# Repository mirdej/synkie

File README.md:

The Synkie is a modular open source analog video processor, developed by Michael Egger, Max Egger and Flo Kaufmann. A bit like the venerable modular Moog synthesizer it lets you toy around with the signal using patch cables – but this time not producing sound but images. It is an instrument for video, a playground, a platform to explore new ways to transform a video signal. Synkie is still in development, we constantly develop new modules – and even the base specifications may still change over time. 

Synkie’s main goal is playability not image quality, even though we try to design each module as best as we can. But patching is done with 2mm laboratory cables – not shielded 75Ohm BNC cables as one would normally use for video. No, you can even use any blank wire and tinker around with the signal in real time on the sk90-breadboard module… The laboratory plugs can be stacked, so you can easily divide the signal into multiple paths, feeding multiple modules at once and change the configuration on the fly. The resulting image can get quite messy down the road, but that’s part of the fun, or maybe even the main purpose…

# Before building stuff from here yourself - read this:

This Github repository is our working space and not a DIY tutorial. Lots of stuff is completely outdated and/or poorly documented. Here are some important notes about the current state of things (Oct 2021):

- Pretty much everything in the EAGLE directory is totally obsolete and we only keep it for documentation.

- We settled on the LMH6643 as our Opamp of choice for almost everything where frequency response matters. Not all schematics reflect this. In most cases if there's an opamp named "generic opamp" or even "LM833" - we probably meant LMH6643.

- There are several modules where the supply connector is flipped. As we etch a lot of boards ourselves there is no silkscreen and we don't see the error. ALWAYS check the polarity !

- We live in PAL land. These modules have not beent tested with NTSC video. Some might need to be adapted slightly, some might even work better than here ;-)

If you have any questions contact <info@synkie.net>

# Basics

## Synkie Backbone
Modules sk000 to sk009 constitute the Synkie Backbone – handling Ins out Outs to the normal Video World. Input video is clamped (black level = GND) and stripped of timing signals and color burst. This signal can then be fed to any processing modules.
In the end , timing signals and a phase corrected color burst is cut back into the modified signal, in sync with the Genlock input.

### sk000-power
Power distribution to backbone modules and rack. +5V, GND, -5V.

### sk001-genlock-in

This module takes any standard video signal as input and generates all necessary timing signals for the Synkie system. The input is first backporch-clamped to GND and all active video is cut off. This black image can serve as a genlock for connected sources (cameras). Colorburst is output as a seperate signal and used to syncronise a quartz crystal that generates a continuous 4.4336Mhz subcarrier signal for the rgb modules. A LM1881 generates the digital sync signals: horizontal sync, vertical sync, backporch and odd/even.

### sk002-input

This modules takes any standard video signal, clamps black level to GND and strips off synctips and colorburst. (still in active debate: me thinks sk002 should apply a gain of 1.43 to bring the 0.7V white level up to 1V)

### sk003-output

This module takes any signal as its input (from DC to 10Mhz). The scale-bias section controls amplitude and dc-shift. The signal is then clipped hard between 0V and 1V. Finally the resyncer adds synctips and colorburst to make it look like a standard video signal. 
When using video as an input to the sk003 any processing beforehand can add some tiny delay - depending on how many modules the signal passes through -  which causes a phase shift in the signal that can alter or completely destroy color. That is why the burst signal from sk001 first goes through a sk004-burstshift (allpass filter) that lets correct the phase error before it gets cut back into the video signal.

## Synkie Signals

### Terminology
| Signal name | Waveform| Description  |Specs|
|---|---|---|---|
|Genlock||A video signal that serves as the master synchronisation signal. Can be routed through and used as an input.|-0.3V to 0.7V|
|Video||Standard PAL video signal|-0.3V to 0.7V|
|Sync| |Digital sync pulses: H-Sync, V-Sync, Backporch, Odd/Even|0V to 5V|
|Burst|| Colorburst only, AC coupled|ca. -0.1V to 0.1V|
|Siff| |Synkie signal. Can be anything, DC, CV, Audio or Video. 0V means black. 1V means white|-1V to 1V|

### The SIFF signal
Synkie's goal is to be able to mix all signals, be it control signals, audio or picture. You should be able to use a video image as control voltage for a VCO like you should be able to inject a sound into the video or watch a steady 0.256 volts.

* Siff signals are DC coupled. 0V means black. 1V means white.
* Siff signals can still be negative, meaning superblack or substracting signals !
* Siff signals can be loud - going beyond 1V and below -1V. The sk003-output module will finally limit the signal to 0-1V.
* Siff signals can range from DC (0Hz) to ca. 10Mhz

This has the following implications for synkie modules:

* All module inputs should be high-impedance, DC coupled and ESR protected.
* All module outputs should be low-impedance and DC coupled.
* Whenever possible a module's bandwidth should be at least 4Mhz
* Sensible CV range should be between 0V and 1V.
* But: Modules must be able to cope with voltages as low as -5V to as high as 5V
* Gate signals are 0V to 1V !!
* So: trigger inputs should trigger at around 0.5V ! Use comparators.

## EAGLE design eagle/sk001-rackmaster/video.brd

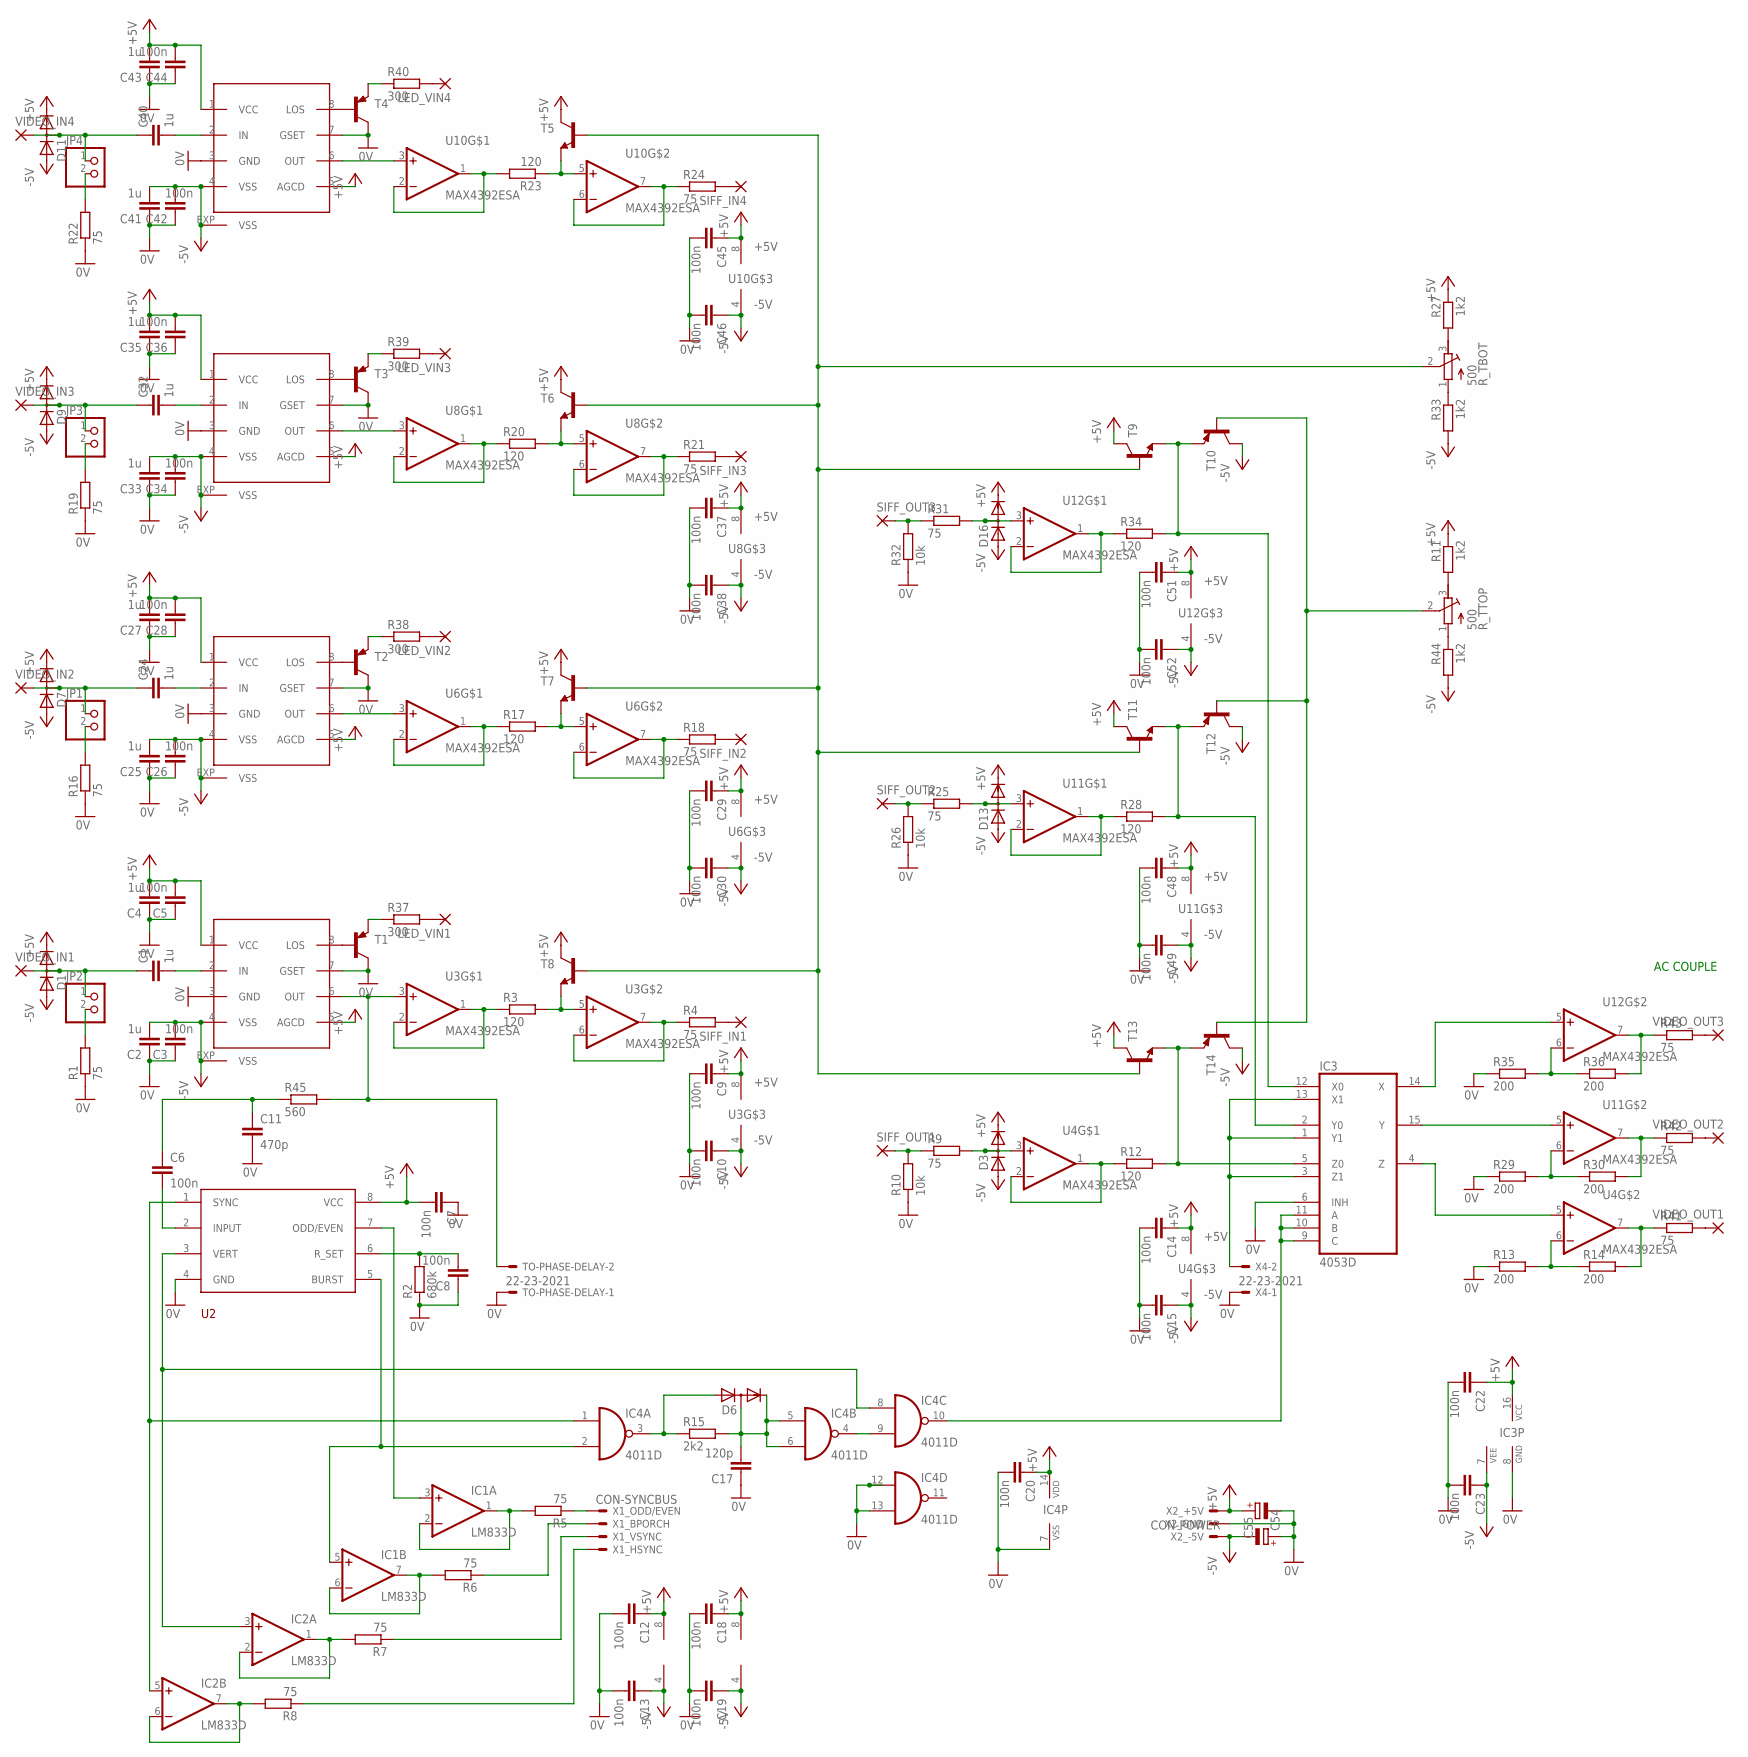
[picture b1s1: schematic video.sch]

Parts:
C1, C2, C4, C24, C25, C27, C32, C33, C35, C40, C41, C43: 1u; C0805
C3, C5, C6, C7, C8, C9, C10, C12, C13, C14, C15, C18, C19, C20, C22, C23, C26, C28, C29, C30, C34, C36, C37, C38, C42, C44, C45, C46, C48, C49, C51, C52: 100n; C0805
C11: 470p; C0805
C17: 120p; C0805
C54, C55: CPOL-EUCT3528; CT3528
D1, D3, D6, D7, D9, D11, D13, D16: DIODE_2CACA-SOT23; SOT23
IC1, IC2: LM833D; SO08
IC3: 4053D; SO16
IC4: 4011D; SO14
JP1, JP2, JP3, JP4: PINHD-1X2; 1X02
LED_VIN1, LED_VIN2, LED_VIN3, LED_VIN4: 3,17/1,1
R1, R4, R5, R6, R7, R8, R9, R16, R18, R19, R21, R22, R24, R25, R31, R41, R42, R43: 75; R0805
R2: 680k; R0805
R3, R12, R17, R20, R23, R28, R34: 120; R0805
R10, R26, R32: 10k; R0805
R11, R27, R33, R44: 1k2; R0805
R13, R14, R29, R30, R35, R36: 200; R0805
R15: 2k2; R0805
R37, R38, R39, R40: 300; R0805
R45: 560; R0805
R_TBOT: 500; RTRIM64Y
R_TTOP: 500; RTRIM64Y
SIFF_IN1, SIFF_IN2, SIFF_IN3, SIFF_IN4: 3,17/1,1
SIFF_OUT1, SIFF_OUT2, SIFF_OUT3: 3,17/1,1
T1, T2, T3, T4, T10, T12, T14: TRANS-PNPSOT23-BEC; SOT23-BEC
T5, T6, T7, T8, T9, T11, T13: TRANS-NPN; SOT23-BEC
TO-PHASE-DELAY: 22-23-2021
U1, U5, U7, U9: MAX7450; SO08-EXP
U2: LM1881SO8; SO08
U3, U4, U6, U8, U10, U11, U12: MAX4392ESA; SO08
VIDEO_IN1, VIDEO_IN2, VIDEO_IN3, VIDEO_IN4: 3,17/1,1
VIDEO_OUT1, VIDEO_OUT2, VIDEO_OUT3: 3,17/1,1
X1: CON-SYNCBUS; 22-23-2041
X2: CON-POWER; 22-23-2031
X4: 22-23-2021

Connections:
0V: C2.1, C3.1, C4.1, C5.1, C7.1, C8.1, C9.2, C10.2, C11.2, C12.2, C13.2, C14.2, C15.2, C17.1, C18.2, C19.2, C20.2, C22.2, C23.2, C25.1, C26.1, C27.1, C28.1, C29.2, C30.2, C33.1, C34.1, C35.1, C36.1, C37.2, C38.2, C41.1, C42.1, C43.1, C44.1, C45.2, C46.2, C48.2, C49.2, C51.2, C52.2, C54.+, C55.-, IC3.6 (INH), IC3.8 (GND), IC4.7 (VSS), IC4.12 (I0), IC4.13 (I1), R1.1, R2.1, R10.1, R13.1, R16.1, R19.1, R22.1, R26.1, R29.1, R32.1, R35.1, T1.C, T2.C, T3.C, T4.C, TO-PHASE-DELAY.1, U1.3 (GND), U1.7 (GSET), U2.4 (GND), U5.3 (GND), U5.7 (GSET), U7.3 (GND), U7.7 (GSET), U9.3 (GND), U9.7 (GSET), X2.2, X4.1
+5V: C4.2, C5.2, C7.2, C9.1, C12.1, C14.1, C18.1, C20.1, C22.1, C27.2, C28.2, C29.1, C35.2, C36.2, C37.1, C43.2, C44.2, C45.1, C48.1, C51.1, C55.+, D1.2 (C), D3.2 (C), D7.2 (C), D9.2 (C), D11.2 (C), D13.2 (C), D16.2 (C), IC1.8 (V+), IC2.8 (V+), IC3.16 (VCC), IC4.14 (VDD), R11.1, R27.1, T5.C, T6.C, T7.C, T8.C, T9.C, T11.C, T13.C, U1.1 (VCC), U1.5 (AGCD), U2.8 (VCC), U3.8 (+5V), U4.8 (+5V), U5.1 (VCC), U5.5 (AGCD), U6.8 (+5V), U7.1 (VCC), U7.5 (AGCD), U8.8 (+5V), U9.1 (VCC), U9.5 (AGCD), U10.8 (+5V), U11.8 (+5V), U12.8 (+5V), X2.3
-5V: C2.2, C3.2, C10.1, C13.1, C15.1, C19.1, C23.1, C25.2, C26.2, C30.1, C33.2, C34.2, C38.1, C41.2, C42.2, C46.1, C49.1, C52.1, C54.-, D1.1 (A), D3.1 (A), D7.1 (A), D9.1 (A), D11.1 (A), D13.1 (A), D16.1 (A), IC1.4 (V-), IC2.4 (V-), IC3.7 (VEE), R33.2, R44.2, T10.C, T12.C, T14.C, U1.4 (VSS), U1.EXP (VSS), U3.4 (-5V), U4.4 (-5V), U5.4 (VSS), U5.EXP (VSS), U6.4 (-5V), U7.4 (VSS), U7.EXP (VSS), U8.4 (-5V), U9.4 (VSS), U9.EXP (VSS), U10.4 (-5V), U11.4 (-5V), U12.4 (-5V), X2.1
H: IC2.5 (+IN), IC4.1 (I0), U2.1 (SYNC)
unnamed: IC3.4 (Z), U4.5 (+IN)
unnamed: JP2.2, R1.2
unnamed: C6.2, U2.2 (INPUT)
unnamed: C8.2, R2.2, U2.6 (R_SET)
unnamed: C1.2, U1.2 (IN)
unnamed: IC1.1 (OUT), IC1.2 (-IN), R5.2
unnamed: R45.2, TO-PHASE-DELAY.2, U1.6 (OUT), U3.3 (+IN)
unnamed: R3.1, U3.1 (OUT), U3.2 (-IN)
unnamed: R3.2, T8.E, U3.5 (+IN)
unnamed: R4.1, U3.6 (-IN), U3.7 (OUT)
unnamed: R4.2, SIFF_IN1.1
unnamed: IC1.6 (-IN), IC1.7 (OUT), R6.2
unnamed: IC2.1 (OUT), IC2.2 (-IN), R7.2
unnamed: IC2.6 (-IN), IC2.7 (OUT), R8.2
unnamed: R6.1, X1.2
unnamed: R5.1, X1.1
unnamed: R7.1, X1.3
unnamed: R8.1, X1.4
unnamed: C6.1, C11.1, R45.1
unnamed: IC1.5 (+IN), IC4.2 (I1), U2.5 (BURST)
unnamed: IC2.3 (+IN), IC4.8 (I0), U2.3 (VERT)
unnamed: R9.1, R10.2, SIFF_OUT1.1
unnamed: D3.3 (AC), R9.2, U4.3 (+IN)
unnamed: R12.1, U4.1 (OUT), U4.2 (-IN)
unnamed: IC3.5 (Z0), R12.2, T13.E, T14.E
unnamed: R27.2, R_TBOT.3 (E)
unnamed: R13.2, R14.1, U4.6 (-IN)
unnamed: C1.1, D1.3 (AC), JP2.1, VIDEO_IN1.1
unnamed: R14.2, R41.1, U4.7 (OUT)
unnamed: IC4.4 (O), IC4.9 (I1)
unnamed: D6.1 (A), IC4.3 (O), R15.1
unnamed: C17.2, D6.2 (C), D6.3 (AC), IC4.5 (I0), IC4.6 (I1), R15.2
unnamed: JP1.2, R16.2
unnamed: R25.1, R26.2, SIFF_OUT2.1
unnamed: C24.2, U5.2 (IN)
unnamed: U5.6 (OUT), U6.3 (+IN)
unnamed: R17.1, U6.1 (OUT), U6.2 (-IN)
unnamed: R17.2, T7.E, U6.5 (+IN)
unnamed: R18.1, U6.6 (-IN), U6.7 (OUT)
unnamed: R18.2, SIFF_IN2.1
unnamed: C24.1, D7.3 (AC), JP1.1, VIDEO_IN2.1
unnamed: JP3.2, R19.2
unnamed: C32.2, U7.2 (IN)
unnamed: U7.6 (OUT), U8.3 (+IN)
unnamed: R20.1, U8.1 (OUT), U8.2 (-IN)
unnamed: R20.2, T6.E, U8.5 (+IN)
unnamed: R21.1, U8.6 (-IN), U8.7 (OUT)
unnamed: R21.2, SIFF_IN3.1
unnamed: C32.1, D9.3 (AC), JP3.1, VIDEO_IN3.1
unnamed: JP4.2, R22.2
unnamed: C40.2, U9.2 (IN)
unnamed: U9.6 (OUT), U10.3 (+IN)
unnamed: R23.2, U10.1 (OUT), U10.2 (-IN)
unnamed: R23.1, T5.E, U10.5 (+IN)
unnamed: R24.1, U10.6 (-IN), U10.7 (OUT)
unnamed: R24.2, SIFF_IN4.1
unnamed: C40.1, D11.3 (AC), JP4.1, VIDEO_IN4.1
unnamed: IC3.9 (C), IC3.10 (B), IC3.11 (A), IC4.10 (O)
unnamed: D13.3 (AC), R25.2, U11.3 (+IN)
unnamed: R28.1, U11.1 (OUT), U11.2 (-IN)
unnamed: R_TTOP.2 (S), T10.B, T12.B, T14.B
unnamed: R33.1, R_TBOT.1 (A)
unnamed: R29.2, R30.1, U11.6 (-IN)
unnamed: R30.2, R42.1, U11.7 (OUT)
unnamed: IC3.15 (Y), U11.5 (+IN)
unnamed: R31.1, R32.2, SIFF_OUT3.1
unnamed: D16.3 (AC), R31.2, U12.3 (+IN)
unnamed: R34.1, U12.1 (OUT), U12.2 (-IN)
unnamed: IC3.12 (X0), R34.2, T9.E, T10.E
unnamed: R11.2, R_TTOP.3 (E)
unnamed: R35.2, R36.1, U12.6 (-IN)
unnamed: R36.2, R43.1, U12.7 (OUT)
unnamed: IC3.14 (X), U12.5 (+IN)
unnamed: R37.1, T1.E
unnamed: LED_VIN1.1, R37.2
unnamed: T1.B, U1.8 (LOS)
unnamed: R38.1, T2.E
unnamed: LED_VIN2.1, R38.2
unnamed: T2.B, U5.8 (LOS)
unnamed: R39.1, T3.E
unnamed: LED_VIN3.1, R39.2
unnamed: T3.B, U7.8 (LOS)
unnamed: R40.1, T4.E
unnamed: LED_VIN4.1, R40.2
unnamed: T4.B, U9.8 (LOS)
unnamed: R41.2, VIDEO_OUT1.1
unnamed: R42.2, VIDEO_OUT2.1
unnamed: R43.2, VIDEO_OUT3.1
unnamed: IC3.1 (Y1), IC3.3 (Z1), IC3.13 (X1), X4.2
unnamed: R_TBOT.2 (S), T5.B, T6.B, T7.B, T8.B, T9.B, T11.B, T13.B
unnamed: IC3.2 (Y0), R28.2, T11.E, T12.E
unnamed: R44.1, R_TTOP.1 (A)
O!E: IC1.3 (+IN), U2.7 (ODD/EVEN)

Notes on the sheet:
AC COUPLE

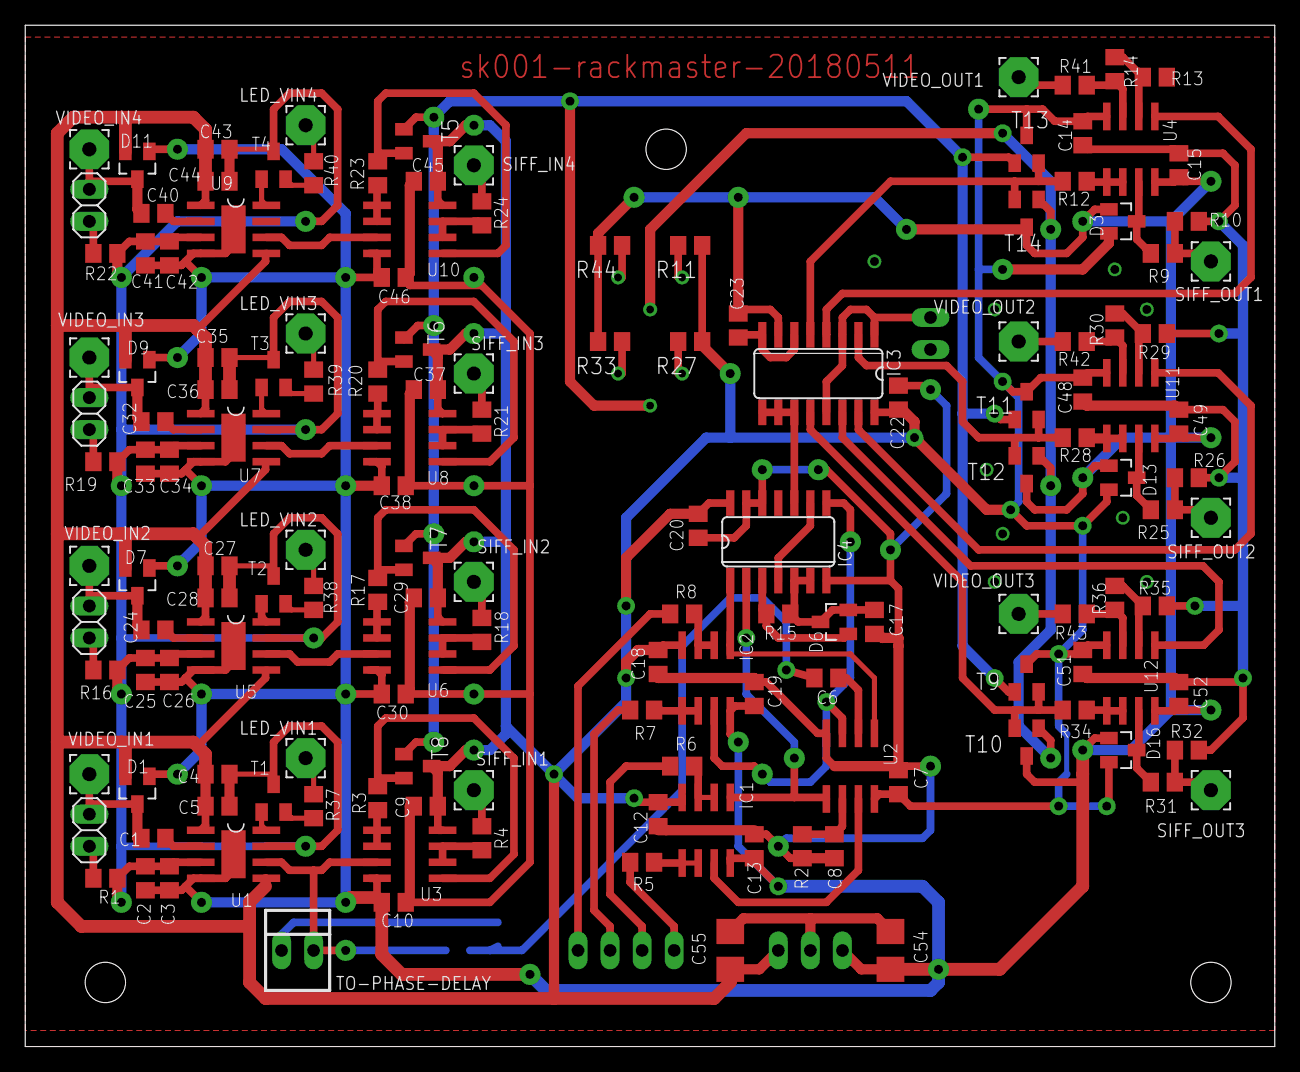
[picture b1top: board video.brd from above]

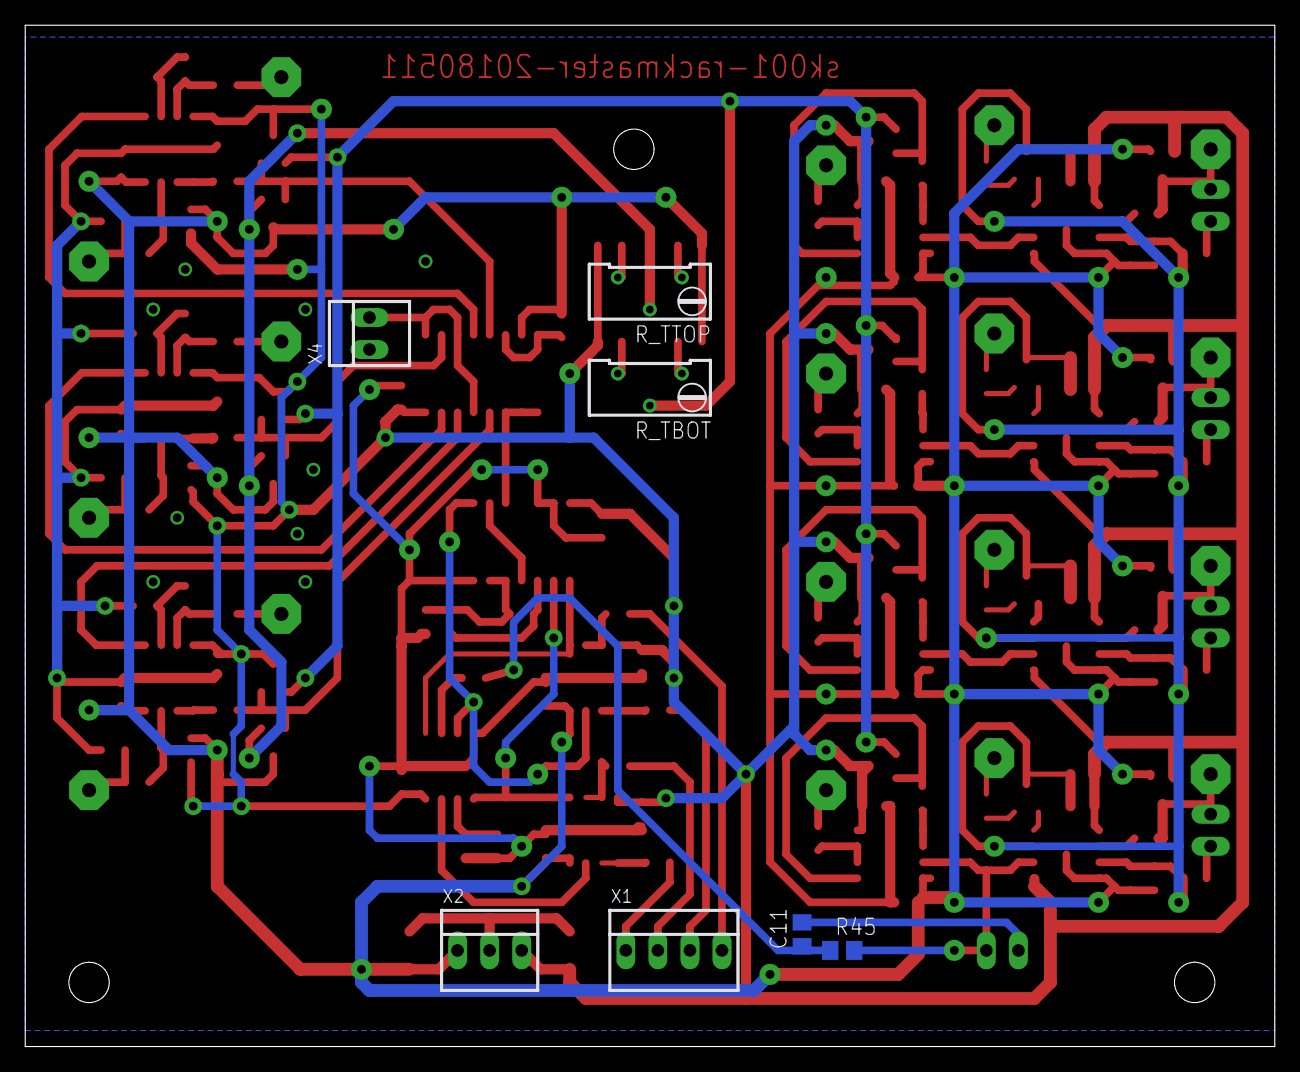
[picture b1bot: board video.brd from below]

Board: 2 copper layers, 99.0 x 81.0 mm, 159 parts (7 on the bottom side), 97 nets.

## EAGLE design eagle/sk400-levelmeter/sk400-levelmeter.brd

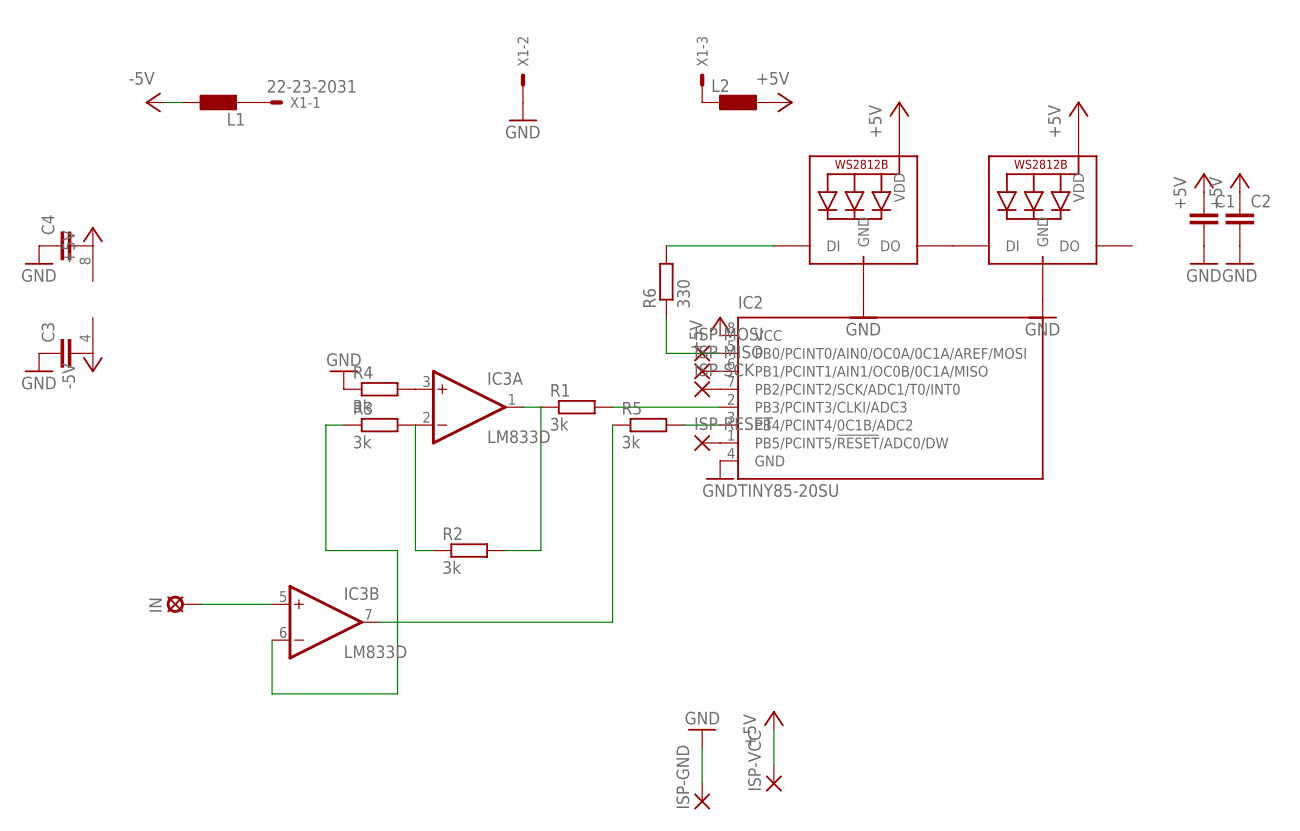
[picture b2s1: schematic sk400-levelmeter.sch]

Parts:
C1, C3, C4: C-EUC1206; C1206
C2: C-EUC0603; C0603
IC2: TINY85-20SU; 8S2
IC3: LM833D; SO08
IN: LSP13
ISP-GND: SMD2
ISP-MISO: SMD2
ISP-MOSI: SMD2
ISP-RESET: SMD2
ISP-SCK: SMD2
ISP-VCC: SMD2
L1, L2: LL2012C; L2012C
R1, R2, R3, R4, R5: 3k; R1206
R6: 330; R1206
U$1, U$2: SK6812MINI
X1: 22-23-2031

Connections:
+5V: C1.1, C2.1, C4.2, IC2.8 (VCC), IC3.8 (V+), ISP-VCC.1, L2.1, U$1.4 (VDD), U$2.4 (VDD)
-5V: C3.2, IC3.4 (V-), L1.1
GND: C1.2, C2.2, C3.1, C4.1, IC2.4 (GND), ISP-GND.1, R4.1, U$1.2 (GND), U$2.2 (GND), X1.2
unnamed: R6.2, U$1.3 (DI)
unnamed: IC2.6 (PB1/PCINT1/AIN1/OC0B/0C1A/MISO), ISP-MISO.1
unnamed: IC2.7 (PB2/PCINT2/SCK/ADC1/T0/INT0), ISP-SCK.1
unnamed: IC2.1 (PB5/PCINT5/!RESET!/ADC0/DW), ISP-RESET.1
unnamed: L1.2, X1.1
unnamed: L2.2, X1.3
unnamed: IC3.1 (OUT), R1.1, R2.2
unnamed: IC3.5 (+IN), IN.MP
unnamed: IC3.3 (+IN), R4.2
unnamed: IC3.2 (-IN), R2.1, R3.2
unnamed: IC2.2 (PB3/PCINT3/CLKI/ADC3), R1.2
unnamed: IC2.3 (PB4/PCINT4/0C1B/ADC2), R5.2
unnamed: U$1.1 (DO), U$2.3 (DI)
unnamed: IC2.5 (PB0/PCINT0/AIN0/OC0A/0C1A/AREF/MOSI), ISP-MOSI.1, R6.1
unnamed: IC3.6 (-IN), IC3.7 (OUT), R3.1, R5.1

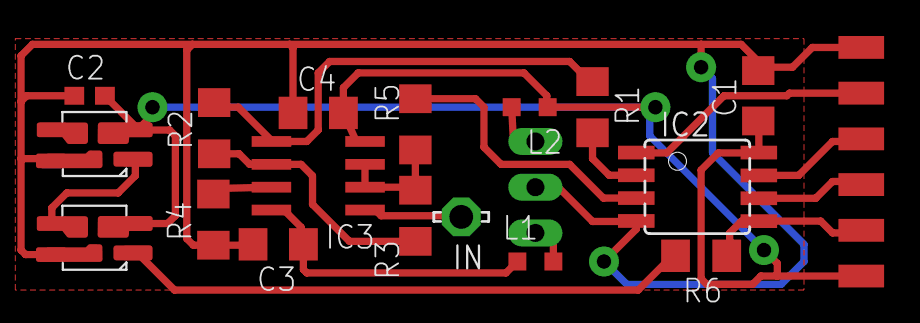
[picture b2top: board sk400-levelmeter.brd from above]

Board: 2 copper layers, 24 parts (1 on the bottom side), 18 nets.

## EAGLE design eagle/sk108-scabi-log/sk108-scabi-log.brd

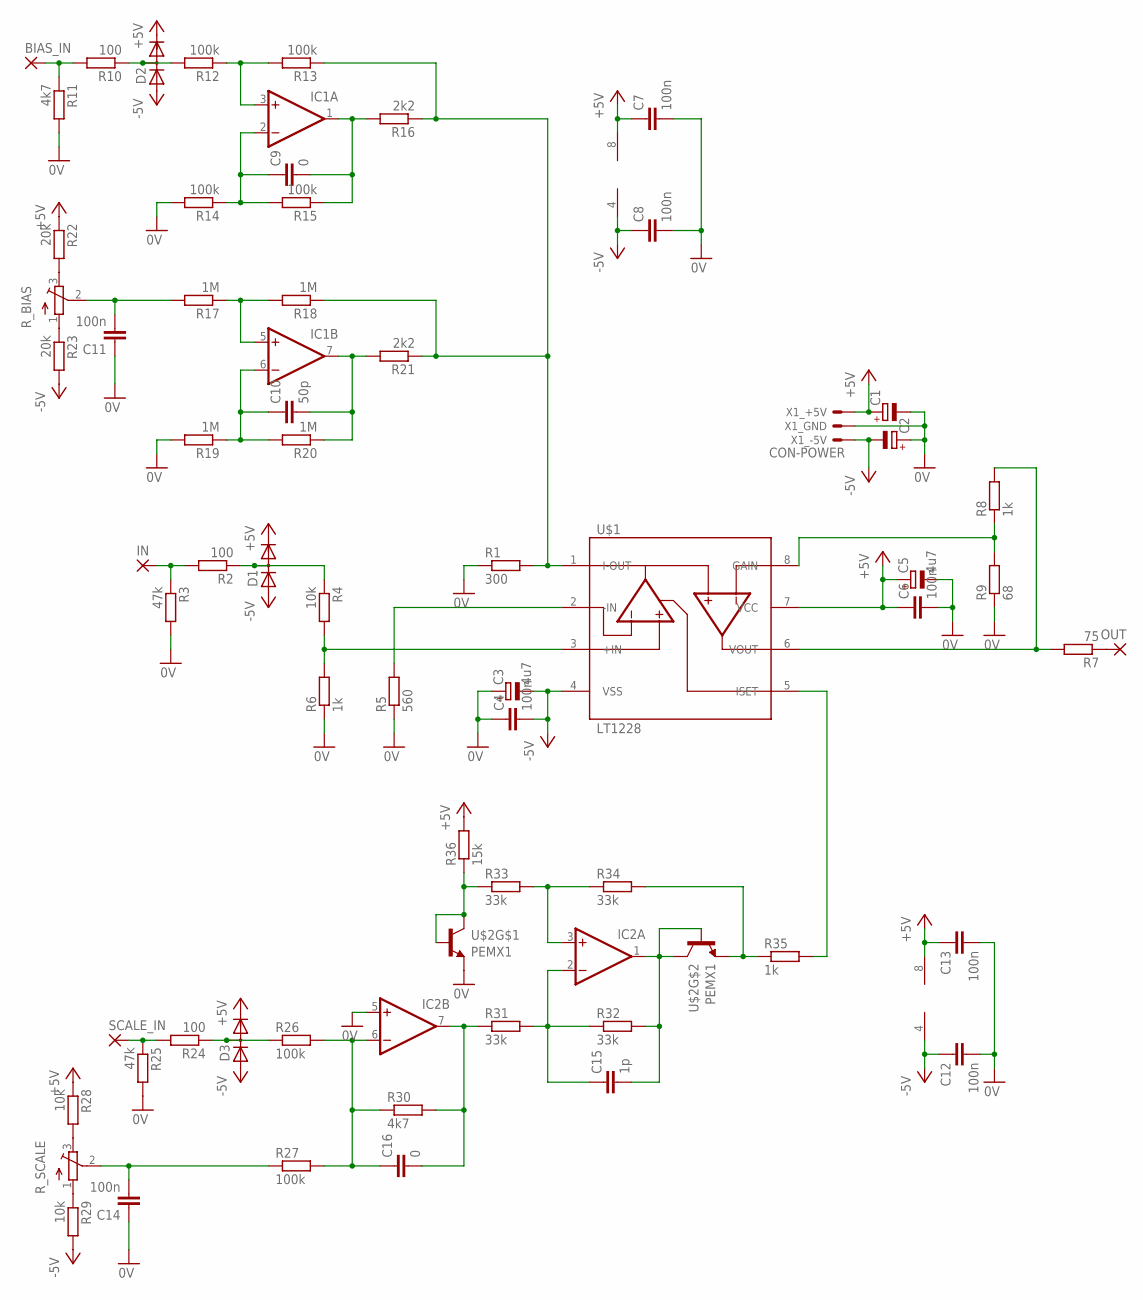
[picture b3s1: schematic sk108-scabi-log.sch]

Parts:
BIAS_IN: 3,17/1,1
C1, C2: CPOL-EUCT3528; CT3528
C3, C5: 4u7; CT3528
C4, C6, C7, C8, C11, C12, C13, C14: 100n; C0805
C9, C16: 0; C0805
C10: 50p; C0805
C15: 1p; C0805
D1, D2, D3: DIODE_2CACA-SOT23; SOT23
IC1, IC2: DUAL_OPAMPD; SO08
IN: 3,17/1,1
OUT: 3,17/1,1
R1: 300; R0805
R2, R10, R24: 100; R0805
R3, R25: 47k; R0805
R4, R28, R29: 10k; R0805
R5: 560; R0805
R6, R8, R35: 1k; R0805
R7: 75; R0805
R9: 68; R0805
R11, R30: 4k7; R0805
R12, R13, R15, R26, R27: 100k; R0805
R14: 100k; R1206
R16, R21: 2k2; R0805
R17, R18, R20: 1M; R0805
R19: 1M; R1206
R22, R23: 20k; R0805
R31, R32, R33, R34: 33k; R0805
R36: 15k; R0805
R_BIAS: ALPS_RK09K111_HOHNE-FüSSE; ALPS_RK09K111
R_SCALE: ALPS_RK09K111_HOHNE-FüSSE; ALPS_RK09K111
SCALE_IN: 3,17/1,1
U$1: LT1228; SO08
U$2: PEMX1; SOT666
X1: CON-POWER; 22-23-2031

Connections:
0V: C1.-, C2.+, C3.+, C4.1, C5.-, C6.2, C7.2, C8.2, C11.1, C12.2, C13.2, C14.1, IC2.5 (+IN), R1.1, R3.2, R5.1, R6.1, R9.1, R11.2, R14.2, R19.2, R25.2, U$2.1 (E), X1.2
+5V: C1.+, C5.+, C6.1, C7.1, C13.1, D1.2 (C), D2.2 (C), D3.2 (C), IC1.8 (V+), IC2.8 (V+), R22.1, R28.1, R36.2, U$1.7 (VCC), X1.3
-5V: C2.-, C3.-, C4.2, C8.1, C12.1, D1.1 (A), D2.1 (A), D3.1 (A), IC1.4 (V-), IC2.4 (V-), R23.2, R29.2, U$1.4 (VSS), X1.1
unnamed: R23.1, R_BIAS.1 (S)
unnamed: IN.1, R2.2, R3.1
unnamed: D1.3 (AC), R2.1, R4.1
unnamed: R4.2, R6.2, U$1.3 (+IN)
unnamed: BIAS_IN.1, R10.2, R11.1
unnamed: R5.2, U$1.2 (-IN)
unnamed: OUT.1, R7.1
unnamed: R7.2, R8.2, U$1.6 (VOUT)
unnamed: R8.1, R9.2, U$1.8 (GAIN)
unnamed: D2.3 (AC), R10.1, R12.2
unnamed: IC1.3 (+IN), R12.1, R13.2
unnamed: C9.1, IC1.2 (-IN), R14.1, R15.2
unnamed: C9.2, IC1.1 (OUT), R15.1, R16.2
unnamed: R1.2, R13.1, R16.1, R18.1, R21.1, U$1.1 (I-OUT)
unnamed: C11.2, R17.2, R_BIAS.2 (W)
unnamed: IC1.5 (+IN), R17.1, R18.2
unnamed: C10.1, IC1.6 (-IN), R19.1, R20.2
unnamed: C10.2, IC1.7 (OUT), R20.1, R21.2
unnamed: R22.2, R_BIAS.3 (E)
unnamed: R24.2, R25.1, SCALE_IN.1
unnamed: D3.3 (AC), R24.1, R26.1
unnamed: C16.1, IC2.6 (-IN), R26.2, R27.2, R30.1
unnamed: R29.1, R_SCALE.1 (S)
unnamed: R28.2, R_SCALE.3 (E)
unnamed: C16.2, IC2.7 (OUT), R30.2, R31.1
unnamed: C15.1, IC2.2 (-IN), R31.2, R32.1
unnamed: C15.2, IC2.1 (OUT), R32.2, U$2.3 (C), U$2.5 (B)
unnamed: R35.2, U$1.5 (ISET)
unnamed: C14.2, R27.1, R_SCALE.2 (W)
unnamed: IC2.3 (+IN), R33.2, R34.1
unnamed: R33.1, R36.1, U$2.2 (B), U$2.6 (C)
unnamed: R34.2, R35.1, U$2.4 (E)

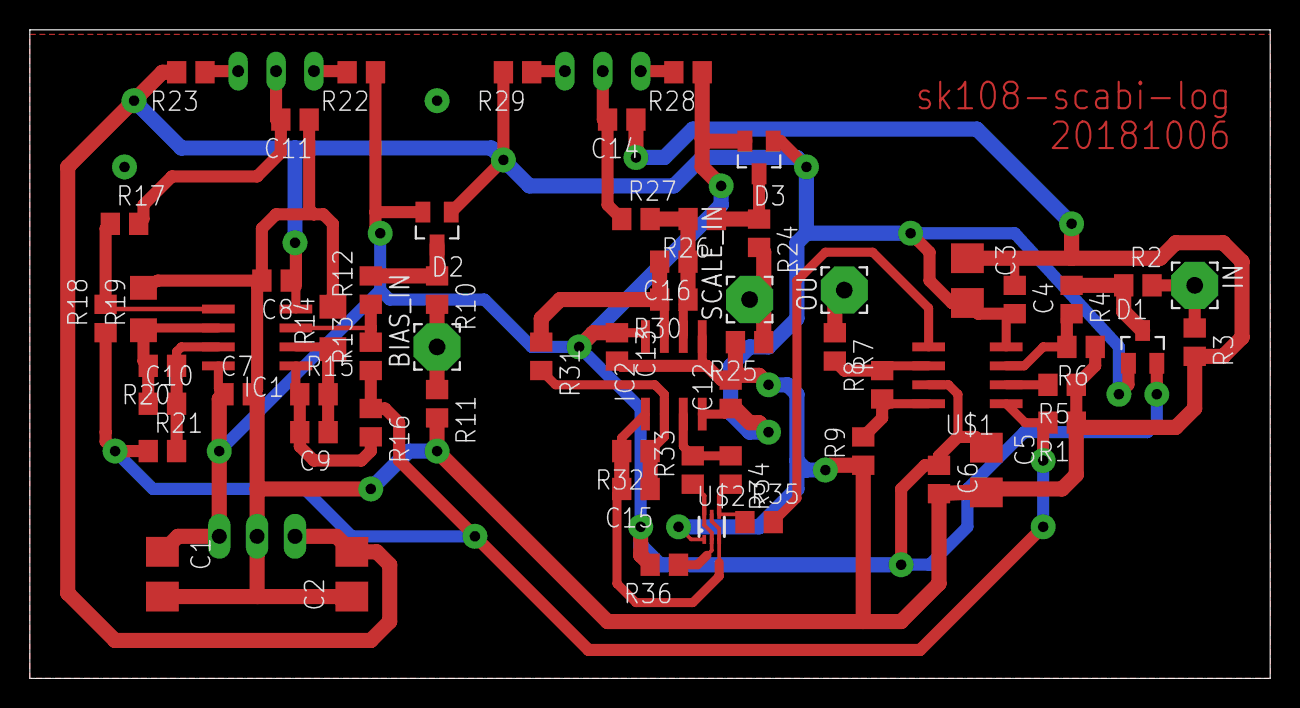
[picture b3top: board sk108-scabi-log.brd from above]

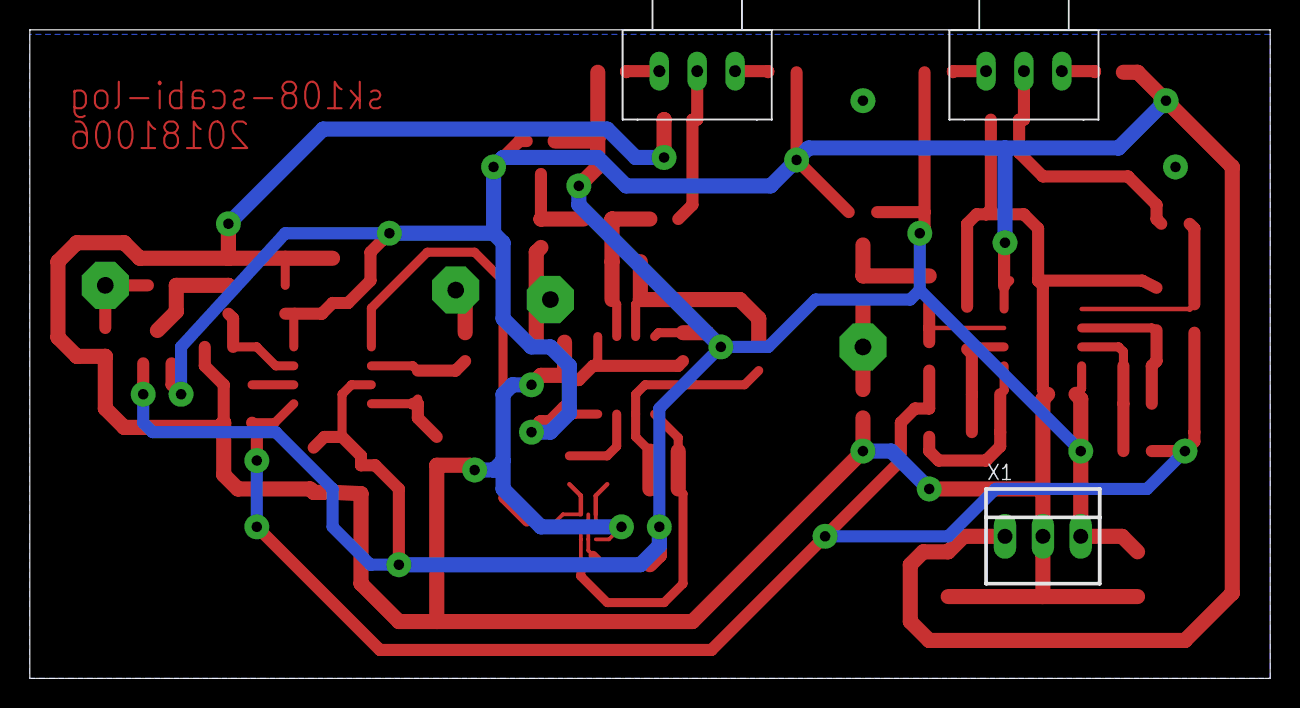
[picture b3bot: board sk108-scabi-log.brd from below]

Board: 2 copper layers, 83.2 x 43.5 mm, 66 parts (3 on the bottom side), 35 nets.
